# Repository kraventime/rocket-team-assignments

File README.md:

PCB Design Assignments given by IITB Rocket Team - Avionics Subsystem:
# BMI160 IMU Breakout Board
Design a 2-layer breakout board for the Bosch BMI160 6-axis IMU (QFN-24 package).
# Basic Flight Computer with Sensors
Design a PCB which can record and store data onboard incorporating:
1.⁠ ⁠RP2040 MCU + W25Q128J flash with SOT package and XIP support + 12 MHz crystal oscillator (10-20 PPM tolerance)
2.⁠ ⁠USB-C port (try to do 90 ohm impedance matching for the differential pairs)
3.⁠ ⁠BMP280 barometric pressure sensor + BMI160 IMU + KX134 high range accelerometer
4.⁠ ⁠Voltage regulators for battery and USB

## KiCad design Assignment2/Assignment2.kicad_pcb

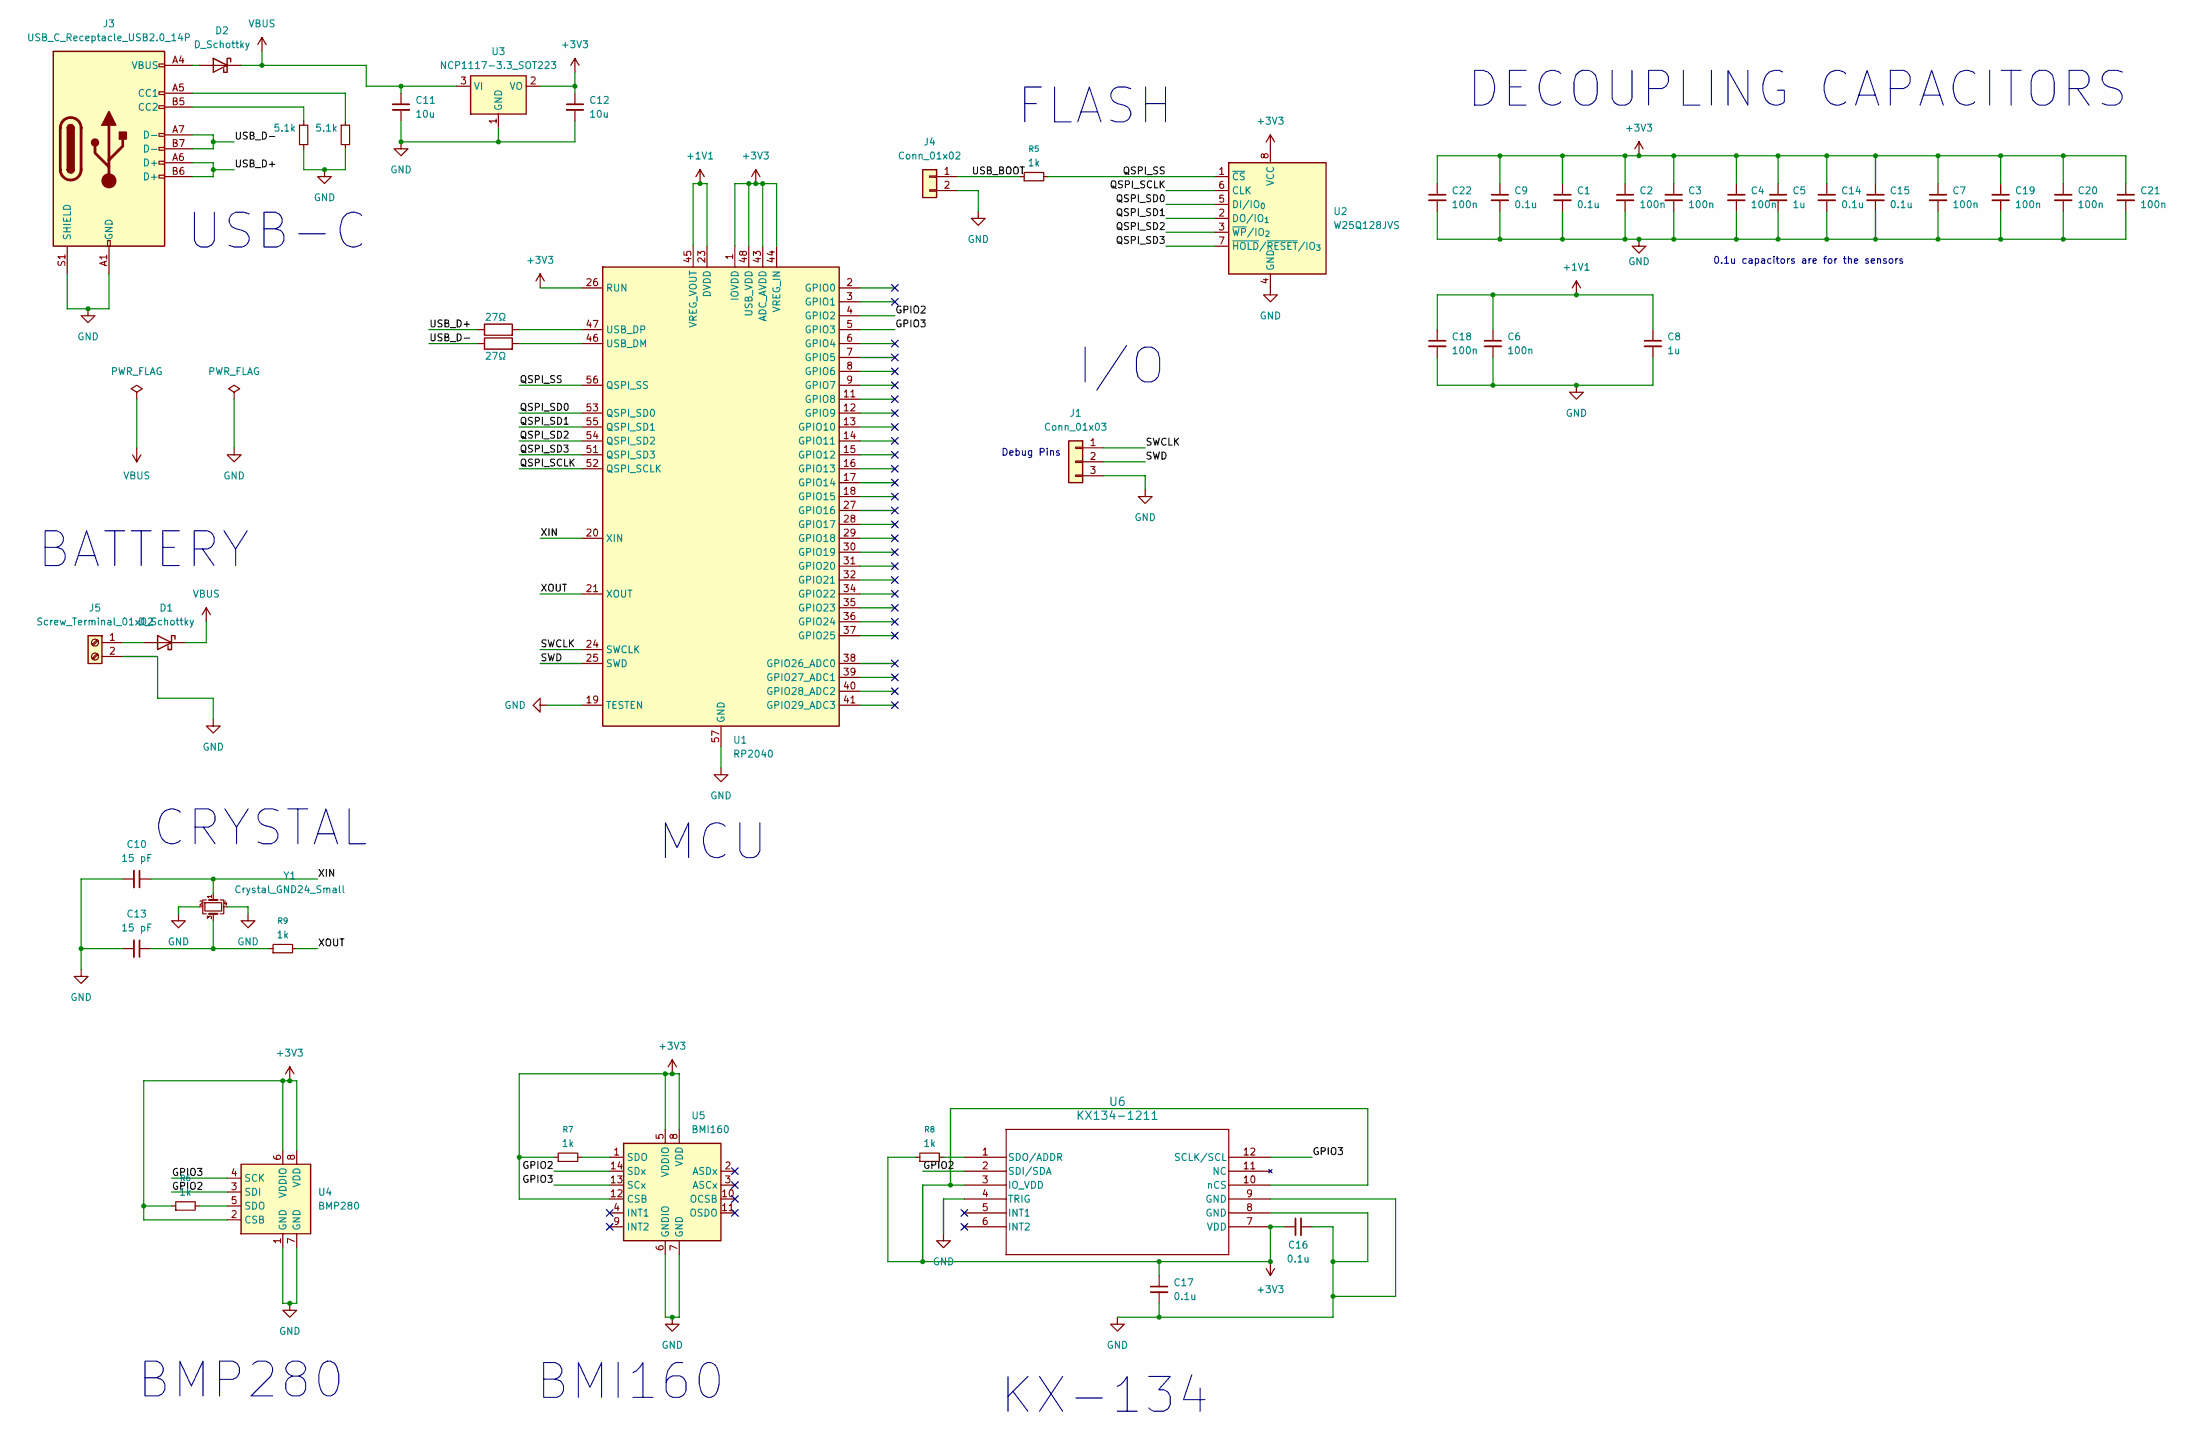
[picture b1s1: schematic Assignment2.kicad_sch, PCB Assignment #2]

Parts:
C1, C9, C14, C15, C16, C17: 0.1u; C_0201_0603Metric
C2, C3, C4, C6, C7, C18, C19, C20, C21, C22: 100n; C_0201_0603Metric
C5, C8: 1u; C_0201_0603Metric
C10, C13: 15 pF; C_0201_0603Metric
C11, C12: 10u; C_0201_0603Metric
D1, D2: D_Schottky; D_2114_3652Metric
J1: Conn_01x03; PinHeader_1x03_P2.54mm_Vertical
J3: USB_C_Receptacle_USB2.0_14P; USB_C_Receptacle_JAE_DX07S016JA1R1500
J4: Conn_01x02; PinHeader_1x02_P2.54mm_Vertical
J5: Screw_Terminal_01x02; TerminalBlock_Phoenix_MPT-0,5-2-2.54_1x02_P2.54mm_Horizontal
R1, R2: 27Ω; R_0201_0603Metric
R3, R4: 5.1k; R_0201_0603Metric
R5, R6, R7, R8, R9: 1k; R_0201_0603Metric
U1: RP2040; QFN-56-1EP_7x7mm_P0.4mm_EP3.2x3.2mm
U2: W25Q128JVS; SOIC-8_5.3x5.3mm_P1.27mm
U3: NCP1117-3.3_SOT223; SOT-223-3_TabPin2
U4: BMP280; Bosch_LGA-8_2x2.5mm_P0.65mm_ClockwisePinNumbering
U5: BMI160; Bosch_LGA-14_3x2.5mm_P0.5mm
U6: KX134-1211; LGA12_2X2X0P9_ROM
Y1: Crystal_GND24_Small; Crystal_SMD_Abracon_ABM10-4Pin_2.5x2.0mm

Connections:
+1V1: C6.1, C8.1, C18.1, U1.23 (DVDD), U1.45 (VREG_VOUT), U1.50 (DVDD)
+3V3: C1.1, C2.1, C3.1, C4.1, C5.1, C7.1, C9.1, C12.1, C14.1, C15.1, C16.1, C17.1, C19.1, C20.1, C21.1, C22.1, R6.1, R7.1, R8.1, U1.1 (IOVDD), U1.10 (IOVDD), U1.22 (IOVDD), U1.26 (RUN), U1.33 (IOVDD), U1.42 (IOVDD), U1.43 (ADC_AVDD), U1.44 (VREG_IN), U1.48 (USB_VDD), U1.49 (IOVDD), U2.8 (VCC), U3.2 (VO), U4.2 (CSB), U4.6 (VDDIO), U4.8 (VDD), U5.5 (VDDIO), U5.8 (VDD), U5.12 (CSB), U6.3 (IO_VDD), U6.7 (VDD), U6.10 (nCS)
/GPIO2: U1.4 (GPIO2), U4.3 (SDI), U5.14 (SDx), U6.2 (SDI/SDA)
/GPIO3: U1.5 (GPIO3), U4.4 (SCK), U5.13 (SCx), U6.12 (SCLK/SCL)
/QSPI_SCLK: U1.52 (QSPI_SCLK), U2.6 (CLK)
/QSPI_SD0: U1.53 (QSPI_SD0), U2.5 (DI/IO_{0})
/QSPI_SD1: U1.55 (QSPI_SD1), U2.2 (DO/IO_{1})
/QSPI_SD2: U1.54 (QSPI_SD2), U2.3 (~WP/IO_{2})
/QSPI_SD3: U1.51 (QSPI_SD3), U2.7 (~HOLD/~RESET/IO_{3})
/QSPI_SS: R5.2, U1.56 (QSPI_SS), U2.1 (~CS)
/SWCLK: J1.1, U1.24 (SWCLK)
/SWD: J1.2, U1.25 (SWD)
/USB_BOOT: J4.1, R5.1
/USB_D+: J3.A6 (D+), J3.B6 (D+), R2.1
/USB_D-: J3.A7 (D-), J3.B7 (D-), R1.1
/XIN: C10.1, U1.20 (XIN), Y1.1
/XOUT: R9.2, U1.21 (XOUT)
GND: C1.2, C2.2, C3.2, C4.2, C5.2, C6.2, C7.2, C8.2, C9.2, C10.2, C11.2, C12.2, C13.2, C14.2, C15.2, C16.2, C17.2, C18.2, C19.2, C20.2, C21.2, C22.2, J1.3, J3.A1 (GND), J3.A12 (GND), J3.B1 (GND), J3.B12 (GND), J3.S1 (SHIELD), J4.2, J5.2, R3.2, R4.2, U1.19 (TESTEN), U1.57 (GND), U2.4 (GND), U3.1 (GND), U4.1 (GND), U4.7 (GND), U5.6 (GNDIO), U5.7 (GND), U6.4 (TRIG), U6.8 (GND), U6.9 (GND), Y1.2, Y1.4
unnamed: C13.1, R9.1, Y1.3
unnamed: D1.2 (A), J5.1
unnamed: D2.2 (A), J3.A4 (VBUS), J3.A9 (VBUS), J3.B4 (VBUS), J3.B9 (VBUS)
unnamed: J3.A5 (CC1), R4.1
unnamed: J3.B5 (CC2), R3.1
unnamed: R1.2, U1.46 (USB_DM)
unnamed: R2.2, U1.47 (USB_DP)
unnamed: R6.2, U4.5 (SDO)
unnamed: R7.2, U5.1 (SDO)
unnamed: R8.2, U6.1 (SDO/ADDR)
VBUS: C11.1, D1.1 (K), D2.1 (K), U3.3 (VI)

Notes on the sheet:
I/O
CRYSTAL
BMP280
MCU
DECOUPLING CAPACITORS
Debug Pins
BMI160
KX-134
FLASH
BATTERY
USB-C
0.1u capacitors are for the sensors

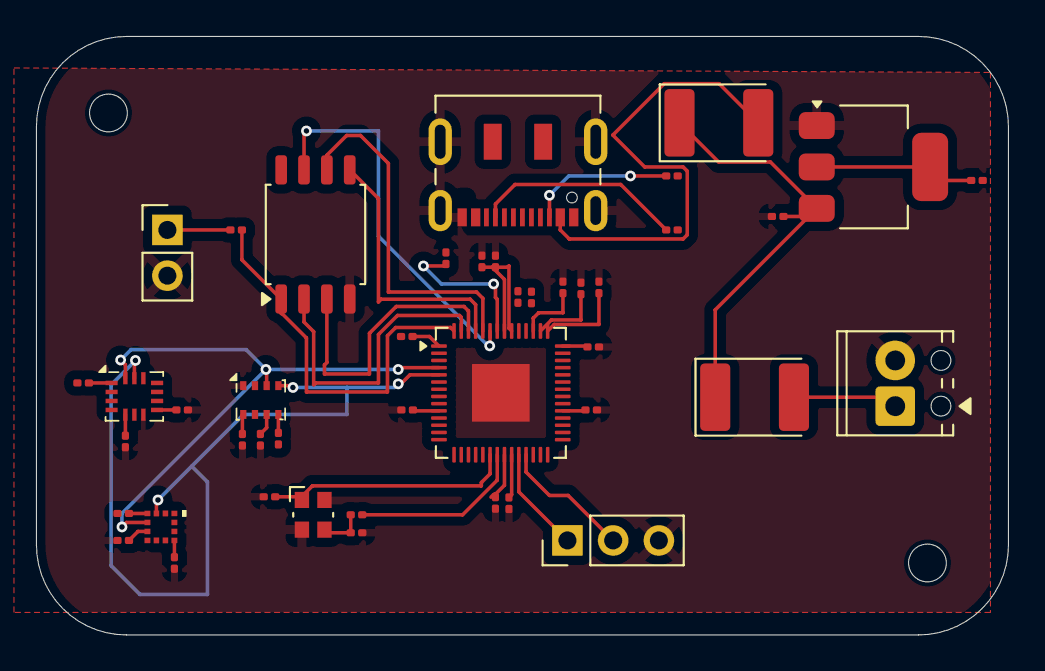
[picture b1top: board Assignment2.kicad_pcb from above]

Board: 2 copper layers, 54.0 x 33.2 mm, 44 parts (0 on the bottom side), 29 nets.

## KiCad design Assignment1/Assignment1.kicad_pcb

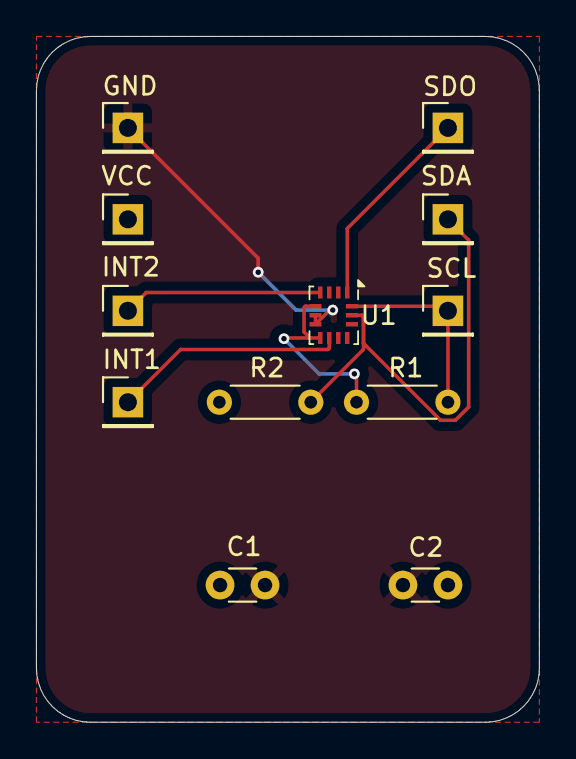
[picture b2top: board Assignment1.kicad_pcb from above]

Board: 2 copper layers, 27.9 x 38.1 mm, 12 parts (0 on the bottom side), 7 nets.

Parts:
C1, C2: 100nF; C_Disc_D3.0mm_W1.6mm_P2.50mm
GND: Conn_01x01_Pin; PinHeader_1x01_P2.54mm_Vertical
INT1: INT1; PinHeader_1x01_P2.54mm_Vertical
INT2: INT2; PinHeader_1x01_P2.54mm_Vertical
R1, R2: R_Small_US; R_Axial_DIN0204_L3.6mm_D1.6mm_P5.08mm_Horizontal
SCL: SCL; PinHeader_1x01_P2.54mm_Vertical
SDA: SDA; PinHeader_1x01_P2.54mm_Vertical
SDO: SDO; PinHeader_1x01_P2.54mm_Vertical
U1: BMI160; Bosch_LGA-14_3x2.5mm_P0.5mm
VCC: Conn_01x01_Pin; PinHeader_1x01_P2.54mm_Vertical

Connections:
GND: C1.2, C2.1, GND.1, U1.6 (GNDIO), U1.7 (GND)
unnamed: INT1.1, U1.4 (INT1)
unnamed: INT2.1, U1.9 (INT2)
unnamed: R2.2, SCL.1, U1.13 (SCx)
unnamed: SDO.1, U1.1 (SDO)
unnamed: R1.2, SDA.1, U1.14 (SDx)
VCC: C1.1, C2.2, R1.1, R2.1, U1.5 (VDDIO), U1.8 (VDD), VCC.1

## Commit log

2026-01-01 Design a breakout board for the BMI-160 IMU
2026-01-01 Add README.md
2026-01-02 Design Schematic for Assignment 2
2026-01-03 Make changes to schematic
2026-01-03 Revise Schematic. Set PCB Constraints
2026-01-04 Arrange PCB elements systematically. Drawing traces still left.
2026-01-05 Join traces. USB Differential Pair still left.
